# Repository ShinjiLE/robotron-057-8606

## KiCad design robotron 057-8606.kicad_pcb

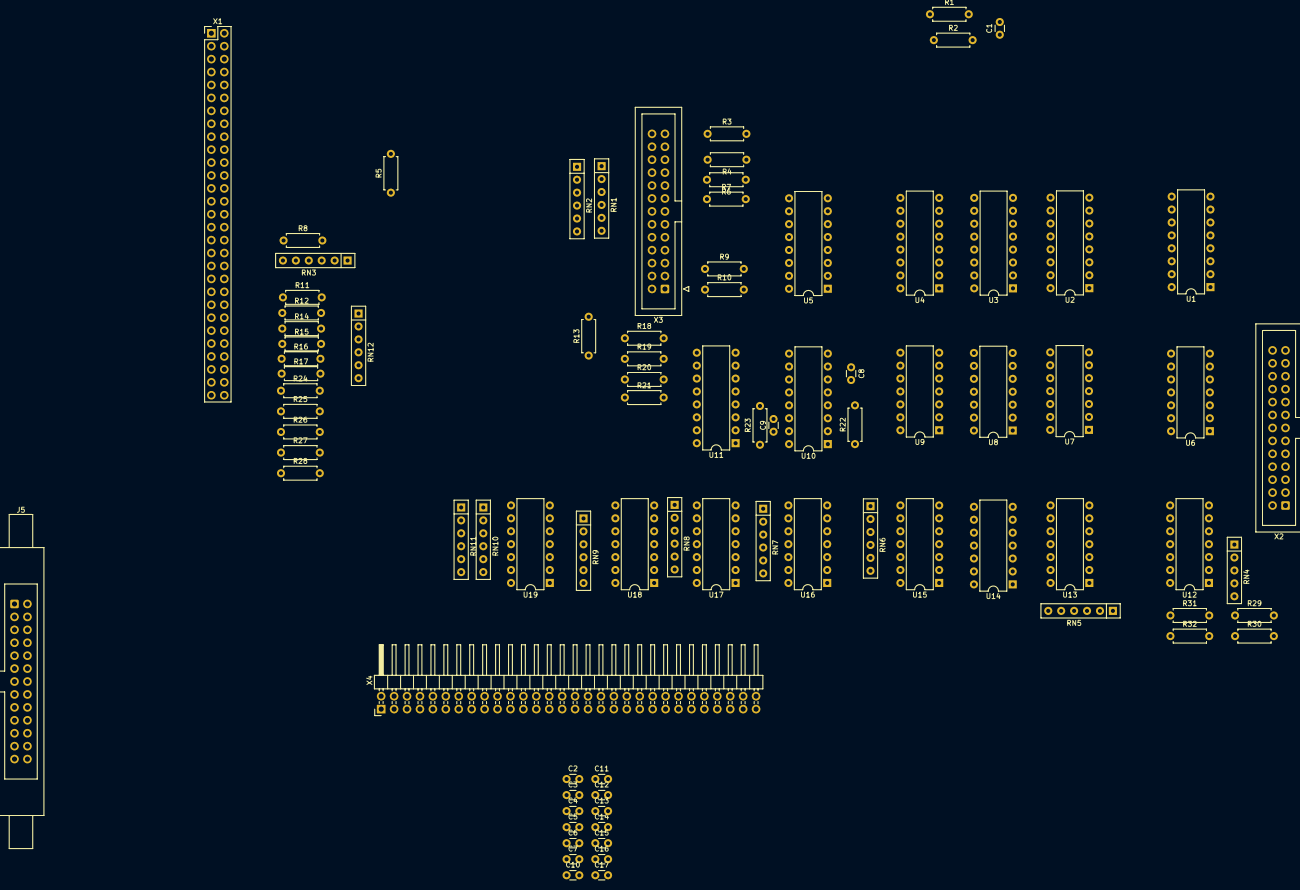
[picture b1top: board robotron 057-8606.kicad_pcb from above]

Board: 2 copper layers, 85 parts (0 on the bottom side), 60 nets, no tracks yet.

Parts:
C1, C2, C3, C4, C5, C6, C7, C8, C9, C10, C11, C12, C13, C14, C15, C16, C17: C_Small; C_Disc_D3.0mm_W1.6mm_P2.50mm
J5: Conn_02x13_Odd_Even; IDC-Header_2x13_P2.54mm_Latch6.5mm_Vertical
R1, R4, R6, R9, R10: 470Ω; R_Axial_DIN0207_L6.3mm_D2.5mm_P7.62mm_Horizontal
R2: 22Ω; R_Axial_DIN0207_L6.3mm_D2.5mm_P7.62mm_Horizontal
R3: 4,7KΩ; R_Axial_DIN0207_L6.3mm_D2.5mm_P7.62mm_Horizontal
R5, R7, R8, R11, R12, R13, R14, R15, R16, R17, R18, R19, R20, R21, R22, R23, R24, R25, R26, R27, R28, R29, R30, R31, R32: R; R_Axial_DIN0207_L6.3mm_D2.5mm_P7.62mm_Horizontal
RN1, RN2, RN3, RN5, RN6, RN7, RN8, RN9, RN10, RN11, RN12: 68Ω; R_Array_SIP6
RN4: R_Array_SIP5
U1, U2, U3, U4, U5, U11: 74LS193; DIP-16_W7.62mm
U6: 74LS04; DIP-14_W7.62mm
U7: 74LS00; DIP-14_W7.62mm
U8: 74LS08; DIP-14_W7.62mm
U9, U12: SN75107; DIP-14_W7.62mm
U10: 74LS123; DIP-16_W7.62mm
U13, U15, U16, U17, U18, U19: SN75110; DIP-14_W7.62mm
U14: 74LS30; DIP-14_W7.62mm
X1: EFS29; PinHeader_2x29_P2.54mm_Vertical
X2: EFS13 Interleaved; IDC-Header_2x13_P2.54mm_Vertical
X3: EFS13; IDC-Header_2x13_P2.54mm_Vertical
X4: Conn_02x30_Top_Bottom; PinHeader_2x30_P2.54mm_Horizontal

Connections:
+5V: R22.1, R23.1, U1.16 (VCC), U2.16 (VCC), U3.16 (VCC), U4.16 (VCC), U5.16 (VCC), U9.14 (VCC+), U11.16 (VCC), U12.14 (VCC+), U13.14 (VCC+), U15.14 (VCC+), U16.14 (VCC+), U17.14 (VCC+), U18.14 (VCC+), U19.14 (VCC+)
-5V: U9.13 (VCC-), U12.13 (VCC-), U13.11 (VCC-), U15.11 (VCC-), U16.11 (VCC-), U17.11 (VCC-), U18.11 (VCC-), U19.11 (VCC-)
/Counter/BIT10_TTL: U5.3 (QA), U15.1 (1A), U15.2 (1B)
/Counter/CLK_UP: U1.5 (UP), U2.5 (UP), U3.5 (UP), U3.15 (A), U4.1 (B), U4.5 (UP), U4.9 (D), U4.10 (C), U4.15 (A), U5.1 (B), U5.5 (UP), U5.9 (D), U5.10 (C), U5.15 (A), U10.2 (B), U10.3 (Clr), U10.10 (B), U10.11 (Clr), U11.5 (UP), U11.15 (A)
/Counter/LOAD_TTL______: U4.11 (~LOAD), U5.11 (~LOAD), U9.4 (1Y)
/Counter/SRV_CLK_TTL: U9.9 (2Y), U14.2
/Counter/UNIT_SELECT_TTL: U3.10 (C), U6.5, U7.9, U12.4 (1Y)
/SERVO-CLK: J5.14, R10.1
//SERVO-CLK: J5.2, R9.1
GND: J5.1, J5.4, J5.7, J5.11, J5.15, J5.18, J5.21, J5.25, R3.2, RN4.1, RN5.1 (common), RN6.1 (common), RN7.1 (common), RN8.1 (common), RN9.1 (common), U1.8 (GND), U2.8 (GND), U2.10 (C), U2.14 (CLR), U3.8 (GND), U3.9 (D), U3.14 (CLR), U4.8 (GND), U4.14 (CLR), U5.8 (GND), U5.14 (CLR), U9.7 (GND), U11.1 (B), U11.8 (GND), U11.9 (D), U11.10 (C), U11.14 (CLR), U12.7 (GND), U13.7 (GND), U15.7 (GND), U16.7 (GND), U17.7 (GND), U18.7 (GND), U19.1 (1A), U19.2 (1B), U19.3 (1C), U19.7 (GND), U19.10 (D)
unnamed: RN5.2 (R1), U13.12 (1Z)
unnamed: RN5.3 (R2), U13.13 (1Y)
unnamed: RN5.5 (R3), U13.9 (2Z)
unnamed: RN5.6 (R4), U13.8 (2Y)
unnamed: RN6.2 (R1), U15.8 (2Y)
unnamed: RN6.3 (R2), U15.9 (2Z)
unnamed: RN6.5 (R3), U15.12 (1Z)
unnamed: RN6.6 (R4), U15.13 (1Y)
unnamed: RN7.2 (R1), U16.9 (2Z)
unnamed: RN7.3 (R2), U16.8 (2Y)
unnamed: RN7.5 (R3), U16.12 (1Z)
unnamed: RN7.6 (R4), U16.13 (1Y)
unnamed: RN8.2 (R1), U17.8 (2Y)
unnamed: RN8.3 (R2), U17.9 (2Z)
unnamed: RN8.5 (R3), U17.12 (1Z)
unnamed: RN8.6 (R4), U17.13 (1Y)
unnamed: RN9.2 (R1), U18.9 (2Z)
unnamed: RN9.3 (R2), U18.8 (2Y)
unnamed: RN9.5 (R3), U18.12 (1Z)
unnamed: RN9.6 (R4), U18.13 (1Y)
unnamed: RN10.5 (R3), U19.8 (2Y)
unnamed: RN10.6 (R4), U19.9 (2Z)
unnamed: U1.1 (B), U1.9 (D), U1.10 (C), U1.14 (CLR), U1.15 (A)
unnamed: U1.4 (DOWN), U8.3
unnamed: U1.7 (QD), U2.4 (DOWN)
unnamed: U1.11 (~LOAD), U2.11 (~LOAD), U3.11 (~LOAD), U11.11 (~LOAD)
unnamed: U2.1 (B), U2.9 (D), U2.15 (A), U3.1 (B), U6.6
unnamed: U2.13 (~BO), U3.4 (DOWN)
unnamed: U4.13 (~BO), U5.4 (DOWN)
unnamed: R9.2, U9.12 (2A)
unnamed: R10.2, U9.11 (2B)
unnamed: U10.1 (A), U10.9 (A)
unnamed: C9.2, U10.14 (Cext)
unnamed: C9.1, R23.2, U10.15 (RCext)
unnamed: U4.4 (DOWN), U8.5, U10.4 (~Q)
unnamed: C8.2, U10.6 (Cext)
unnamed: C8.1, R22.2, U10.7 (RCext)
unnamed: U3.13 (~BO), U11.4 (DOWN)
unnamed: RN4.4, U12.1 (1A)
unnamed: RN4.3, U12.2 (1B)
unnamed: U12.5 (1G), U12.6 (S)
unnamed: R6.1, U12.12 (2A)
unnamed: R4.1, U12.11 (2B)
unnamed: U13.1 (1A), U13.2 (1B)
unnamed: U13.3 (1C), U13.4 (2C), U13.10 (D), U15.3 (1C), U15.4 (2C), U15.10 (D), U16.1 (1A), U16.4 (2C), U16.10 (D), U17.2 (1B), U17.3 (1C), U17.4 (2C), U17.5 (2A), U17.10 (D), U18.2 (1B), U18.3 (1C), U18.4 (2C), U18.5 (2A), U18.10 (D), U19.4 (2C)
unnamed: U13.5 (2A), U13.6 (2B)
unnamed: U15.5 (2A), U15.6 (2B)
unnamed: U16.2 (1B), U16.3 (1C)
unnamed: U16.5 (2A), U16.6 (2B)
unnamed: U19.5 (2A), U19.6 (2B)

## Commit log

2024-08-27 Einige Verbindungen im Bereich des Zählers ermittelt
2024-08-28 Aufnahme Schaltplan wip
2024-09-02 rev eng wip
2024-09-04 Busses Names and more
2024-09-18 weitere verdrahtungen nachvollzogen
